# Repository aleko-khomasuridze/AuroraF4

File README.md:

# AuroraF4

AuroraF4 is a powerful development board based on the STM32F407VGT microcontroller, designed to provide developers with a feature-rich and compact solution for embedded system projects. This board is equipped with multiple peripherals, GPIOs, and expansion headers, making it ideal for both beginners and professionals.

## Features

- **Microcontroller**: STM32F407VGT
  - ARM Cortex-M4 processor
  - 168 MHz clock speed
  - 1 MB Flash, 192 KB SRAM
- **Interfaces**:
  - SPI, I2C, USART
  - JTAG/SWD debugging support
- **Peripherals**:
  - User-configurable LEDs (Green, Red, Yellow, Blue)
  - Reset (RST) and User (USR) buttons
  - Power input via USB-C or barrel jack
- **Expansion**:
  - Pin headers for GPIO access
  - 3.3V and GND pins available for peripherals
- **Power**:
  - Powered via USB-C or external 12V input

## Pinout Diagram

Refer to the pinout diagram above for GPIO assignments and interface connections.

## PCB Design and Layout

### PCB Top View

### 3D Render

## Getting Started

### Prerequisites

- Install [STM32CubeIDE](https://www.st.com/en/development-tools/stm32cubeide.html) for firmware development.
- Set up the STM32CubeMX tool for peripheral configuration.

### Powering the Board

1. Connect a USB-C cable to the power port.
2. Alternatively, use a 12V adapter through the barrel jack.

### Flashing Code

1. Connect the board to   your computer via USB.
2. Open STM32CubeIDE, configure your project for the STM32F407VGT.
3. Build and flash your program to the board.

### Debugging

Use the JTAG/SWD interface for debugging and programming. Ensure you have a compatible debugger like ST-Link V2.

## Applications

AuroraF4 is suitable for:
- Embedded systems prototyping
- IoT projects
- Robotics and automation
- Learning and experimentation with ARM Cortex-M4 architecture

## Resources

- [STM32F407VGT Datasheet](https://www.st.com/resource/en/datasheet/stm32f407vg.pdf)
- [STM32CubeIDE](https://www.st.com/en/development-tools/stm32cubeide.html)
- Pinout and Schematic: Refer to the `pinout.jpg` and PCB layout images in this repository.

## Credits

AuroraF4 is designed and assembled in Georgia by Aleko Khomasuridze.

---

For questions, suggestions, or contributions, feel free to open an issue or reach out.

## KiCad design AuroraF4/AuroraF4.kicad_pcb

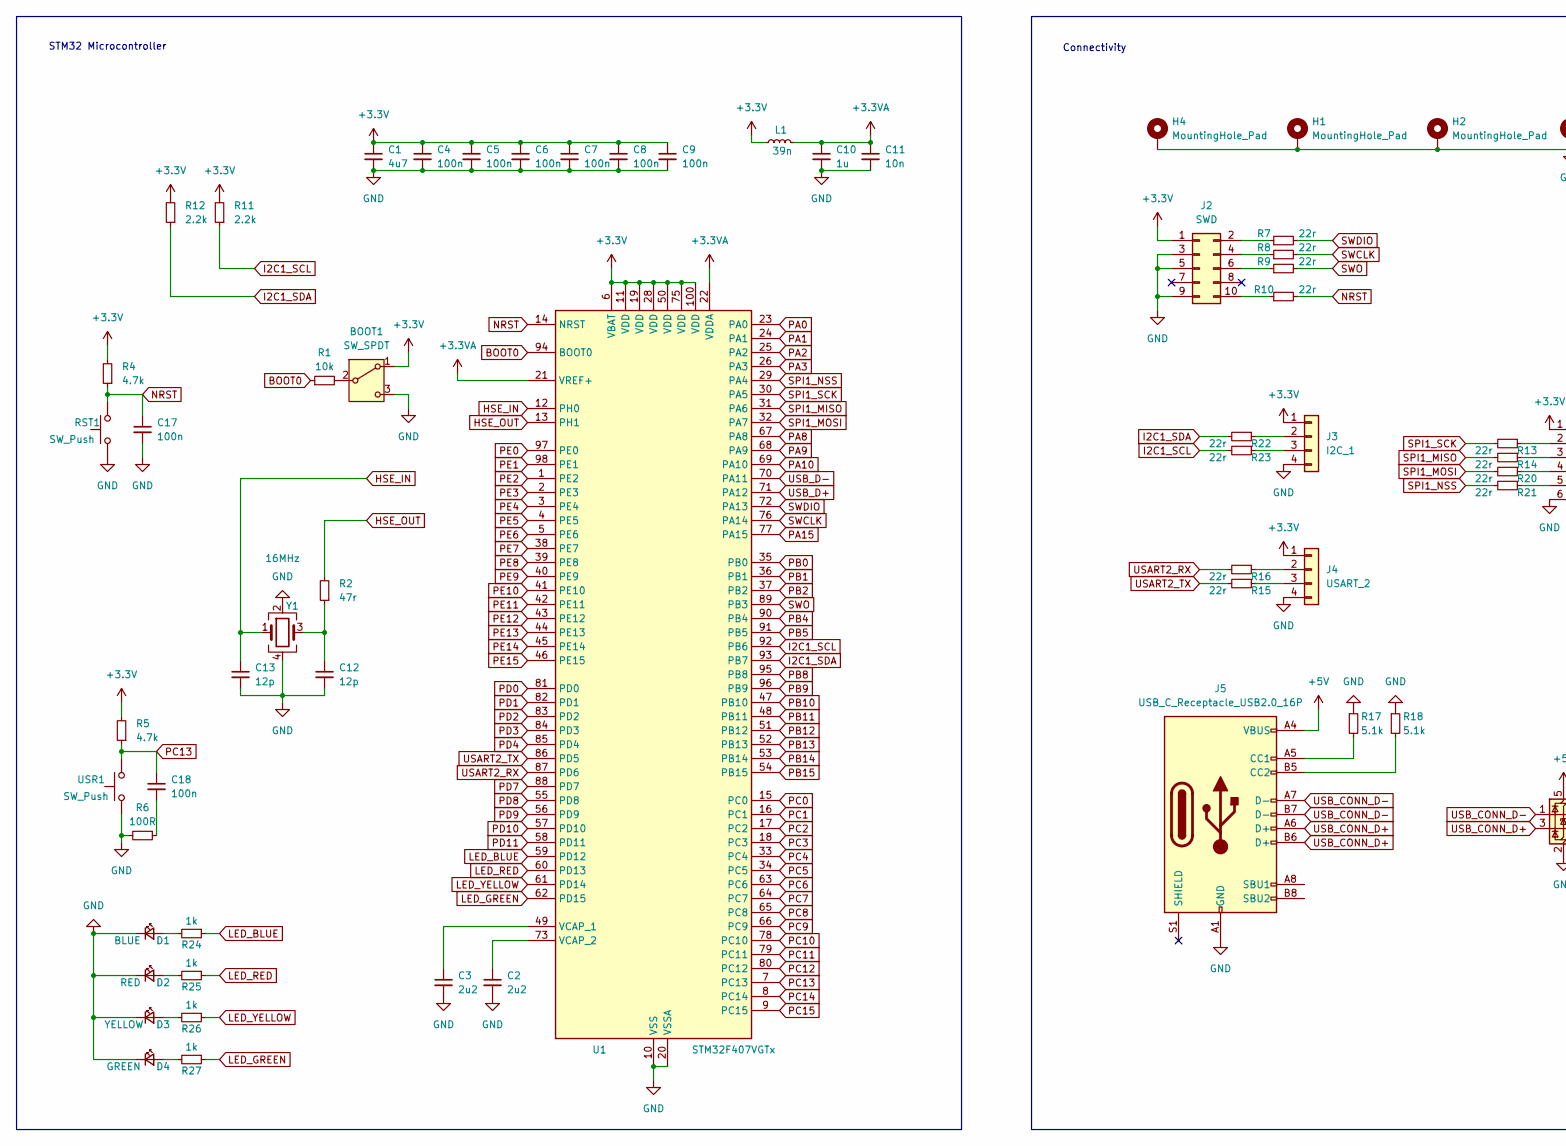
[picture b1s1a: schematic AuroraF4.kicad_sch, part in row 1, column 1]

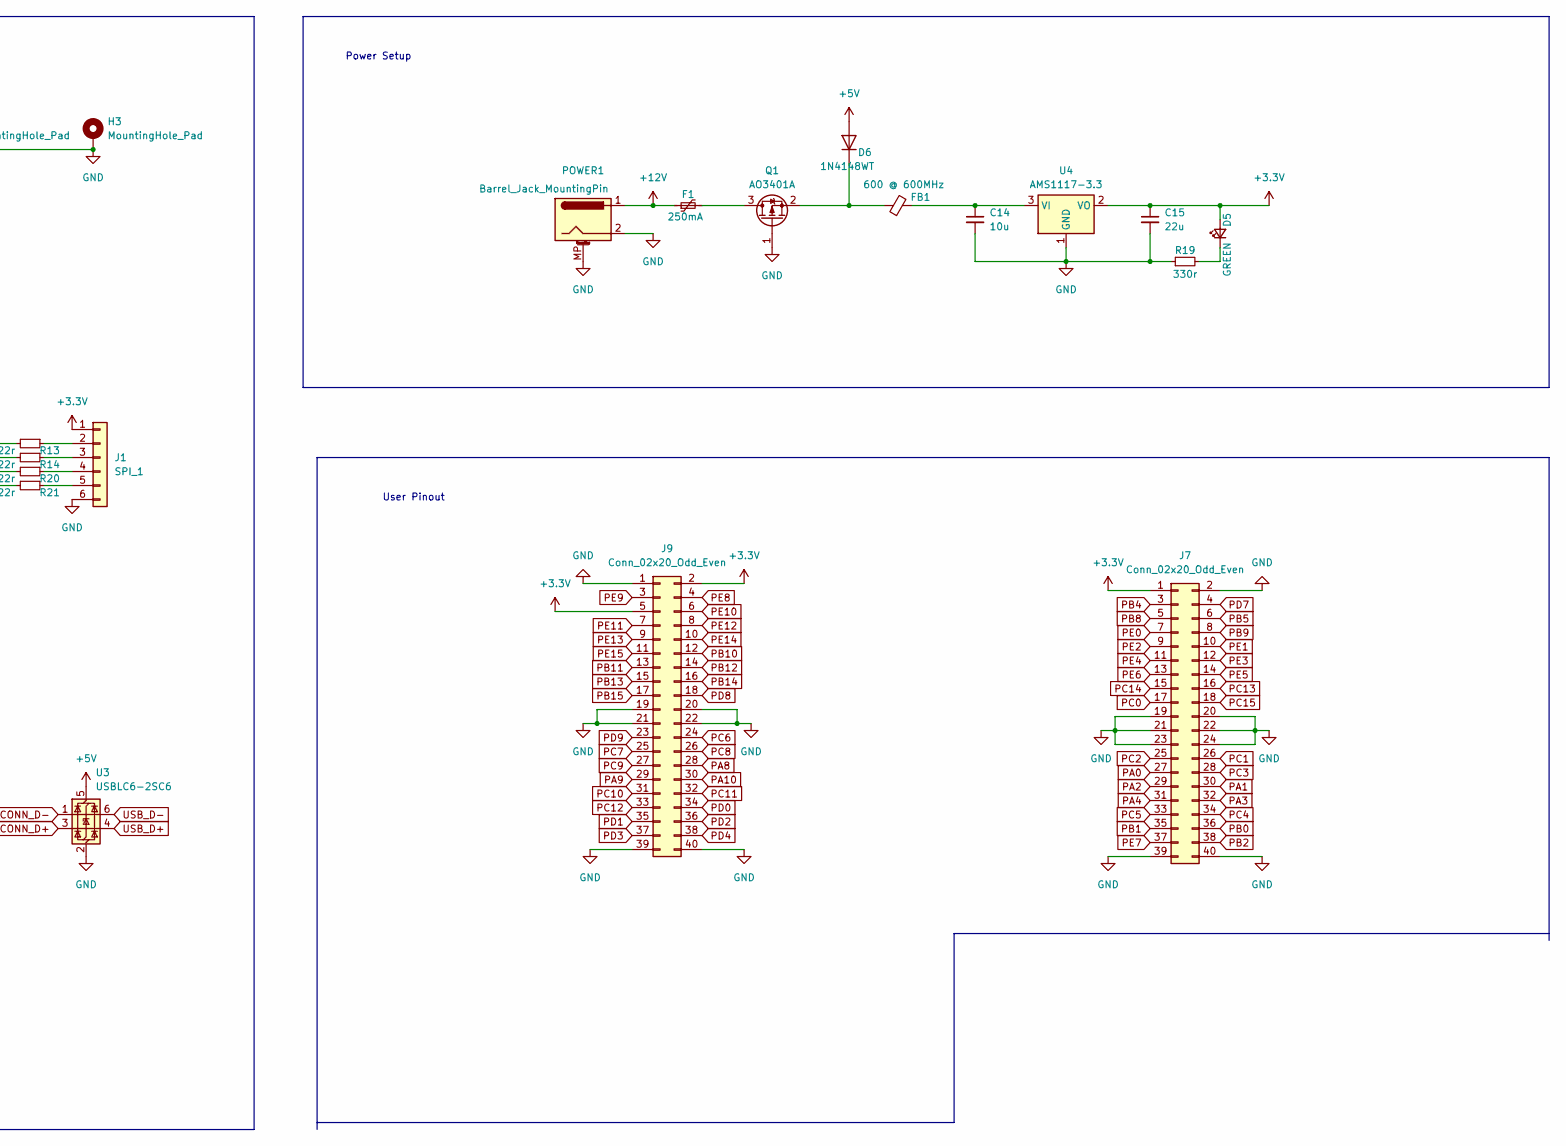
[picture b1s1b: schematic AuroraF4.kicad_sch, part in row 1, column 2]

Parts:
BOOT1: SW_SPDT; SW_SPDT_PCM12; LCSC Part # C221841
C1: 4u7; C_0603_1608Metric; LCSC Part # C1705
C2, C3: 2u2; C_0603_1608Metric; LCSC Part # C23630
C4, C5, C6, C7, C8, C9, C17, C18: 100n; C_0603_1608Metric; LCSC Part # C14663
C10: 1u; C_0603_1608Metric; LCSC Part # C1592
C11: 10n; C_0603_1608Metric; LCSC Part # C100042
C12, C13: 12p; C_0603_1608Metric; LCSC Part # C107034
C14: 10u; C_0805_2012Metric; LCSC Part # C5189822
C15: 22u; C_0805_2012Metric; LCSC Part # C29277
D1: BLUE; LED_0603_1608Metric; LCSC Part # C72041
D2: RED; LED_0603_1608Metric; LCSC Part # C72044
D3: YELLOW; LED_0603_1608Metric; LCSC Part # C72038
D4, D5: GREEN; LED_0603_1608Metric; LCSC Part # C72043
D6: 1N4148WT; D_SOD-123; LCSC Part # C963381
F1: 250mA; Fuse_1206_3216Metric; LCSC Part # C135328
FB1: 600 @ 600MHz; L_0805_2012Metric; LCSC Part # C1017
H1, H2, H3, H4: MountingHole_Pad; MountingHole_3.2mm_M3_Pad_Via
J1: SPI_1; JST-XA-1.25mm SMD Horizontal 01x06
J2: SWD; PinHeader_2x05_P1.27mm_Vertical_SMD; LCSC Part # C598540
J3: I2C_1; JST-XA-1.25mm SMD Horizontal 01x04
J4: USART_2; JST-XA-1.25mm SMD Horizontal 01x04
J5: USB_C_Receptacle_USB2.0_16P; USB_C_Receptacle_HCTL_HC-TYPE-C-16P-01A; LCSC Part # C39832533
J7, J9: Conn_02x20_Odd_Even; PinHeader_2x20_P2.54mm_Vertical
L1: 39n; L_0603_1608Metric; LCSC Part # C74308
POWER1: Barrel_Jack_MountingPin; BarrelJack_GCT_DCJ200-10-A_Horisontal; LCSC Part # C319099
Q1: AO3401A; SOT-23; LCSC Part # C347476
R1: 10k; R_0603_1608Metric; LCSC Part # C25804
R2: 47r; R_0603_1608Metric; LCSC Part # C23182
R4, R5: 4.7k; R_0603_1608Metric; LCSC Part # C105428
R6: 100R; R_0603_1608Metric; LCSC Part # C23345
R7, R8, R9, R10, R13, R14, R15, R16, R20, R21, R22, R23: 22r; R_0603_1608Metric; LCSC Part # C23345
R11, R12: 2.2k; R_0603_1608Metric; LCSC Part # C4190
R17, R18: 5.1k; R_0603_1608Metric; LCSC Part # C23186
R19: 330r; R_0603_1608Metric; LCSC Part # C23138
R24, R25, R26, R27: 1k; R_0603_1608Metric; LCSC Part # C25804
RST1: SW_Push; SW_SPST_B3U-1000P; LCSC Part # C843666
U1: STM32F407VGTx; LQFP-100_14x14mm_P0.5mm; LCSC Part # C12345
U3: USBLC6-2SC6; SOT-23-6; LCSC Part # C7519
U4: AMS1117-3.3; SOT-223-3_TabPin2; LCSC Part # C347222
USR1: SW_Push; SW_SPST_B3U-1000P; LCSC Part # C843666
Y1: 16MHz; Crystal_SMD_3225-4Pin_3.2x2.5mm; LCSC Part # C5917307

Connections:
+3.3V: BOOT1.1 (A), C1.1, C4.1, C5.1, C6.1, C7.1, C8.1, C9.1, C15.1, D5.2 (A), J1.1, J2.1, J3.1, J4.1, J7.1, J9.2, J9.5, L1.1, R4.2, R5.2, R11.2, R12.2, U1.6 (VBAT), U1.11 (VDD), U1.19 (VDD), U1.28 (VDD), U1.50 (VDD), U1.75 (VDD), U1.100 (VDD), U4.2 (VO)
+3.3VA: C10.1, C11.1, L1.2, U1.21 (VREF+), U1.22 (VDDA)
+5V: D6.2 (A), J5.A4 (VBUS), J5.A9 (VBUS), J5.B4 (VBUS), J5.B9 (VBUS), U3.5 (VBUS)
+12V: F1.1, POWER1.1; also elsewhere on the board
BOOT0: R1.1, U1.94 (BOOT0)
GND: BOOT1.3 (C), C1.2, C2.2, C3.2, C4.2, C5.2, C6.2, C7.2, C8.2, C9.2, C10.2, C11.2, C12.2, C13.2, C14.2, C15.2, C17.2, D1.1 (K), D2.1 (K), D3.1 (K), D4.1 (K), H1.1, H2.1, H3.1, H4.1, J1.6, J2.3, J2.5, J2.9, J3.4, J4.4, J5.A1 (GND), J5.A12 (GND), J5.B1 (GND), J5.B12 (GND), J7.2, J7.19, J7.20, J7.21, J7.22, J7.23, J7.24, J7.39, J7.40, J9.1, J9.19, J9.20, J9.21, J9.22, J9.39, J9.40, POWER1.2, POWER1.MP (MountPin), Q1.1 (G), R6.2, R17.1, R18.1, R19.1, RST1.1, U1.10 (VSS), U1.20 (VSSA), U1.27 (VSS), U1.74 (VSS), U1.99 (VSS), U3.2 (GND), U4.1 (GND), USR1.1, Y1.2, Y1.4; also elsewhere on the board
HSE_IN: C13.1, U1.12 (PH0), Y1.1
HSE_OUT: R2.2, U1.13 (PH1)
I2C1_SCL: R11.1, R23.2, U1.92 (PB6)
I2C1_SDA: R12.1, R22.2, U1.93 (PB7)
LED_BLUE: R24.1, U1.59 (PD12)
LED_GREEN: R27.1, U1.62 (PD15)
LED_RED: R25.1, U1.60 (PD13)
LED_YELLOW: R26.1, U1.61 (PD14)
NRST: C17.1, R4.1, R10.2, RST1.2, U1.14 (NRST); also elsewhere on the board
unnamed: BOOT1.2 (B), R1.2
unnamed: C12.1, R2.1, Y1.3
unnamed: C18.2, R6.1
unnamed: D1.2 (A), R24.2
unnamed: D2.2 (A), R25.2
unnamed: D3.2 (A), R26.2
unnamed: D4.2 (A), R27.2
unnamed: D5.1 (K), R19.2
unnamed: D6.1 (K), FB1.1, Q1.2 (S)
unnamed: J1.2, R13.1
unnamed: J1.3, R14.1
unnamed: J1.4, R20.1
unnamed: J1.5, R21.1
unnamed: J2.2, R7.1
unnamed: J2.4, R8.1
unnamed: J2.6, R9.1
unnamed: J2.10, R10.1
unnamed: J3.2, R22.1
unnamed: J3.3, R23.1
unnamed: J4.2, R16.1
unnamed: J4.3, R15.1
unnamed: J5.A5 (CC1), R17.2
unnamed: J5.B5 (CC2), R18.2
unnamed: F1.2, Q1.3 (D)
unnamed: C3.1, U1.49 (VCAP_1)
unnamed: C2.1, U1.73 (VCAP_2)
unnamed: C14.1, FB1.2, U4.3 (VI)
PA0: J7.27, U1.23 (PA0)
PA1: J7.30, U1.24 (PA1)
PA2: J7.29, U1.25 (PA2)
PA3: J7.32, U1.26 (PA3)
PA4: J7.31
PA8: J9.28, U1.67 (PA8)
PA9: J9.29, U1.68 (PA9)
PA10: J9.30, U1.69 (PA10)
PA15: U1.77 (PA15)
PB0: J7.36, U1.35 (PB0)
PB1: J7.35, U1.36 (PB1)
PB2: J7.38, U1.37 (PB2)
PB4: J7.3, U1.90 (PB4)
PB5: J7.6, U1.91 (PB5)
PB8: J7.5, U1.95 (PB8)
PB9: J7.8, U1.96 (PB9)
PB10: J9.12, U1.47 (PB10)
PB11: J9.13, U1.48 (PB11)
PB12: J9.14, U1.51 (PB12)
PB13: J9.15, U1.52 (PB13)
PB14: J9.16, U1.53 (PB14)
PB15: J9.17, U1.54 (PB15)
PC0: J7.17, U1.15 (PC0)
PC1: J7.26, U1.16 (PC1)
PC2: J7.25, U1.17 (PC2)
PC3: J7.28, U1.18 (PC3)
PC4: J7.34, U1.33 (PC4)
PC5: J7.33, U1.34 (PC5)
PC6: J9.24, U1.63 (PC6)
PC7: J9.25, U1.64 (PC7)
PC8: J9.26, U1.65 (PC8)
PC9: J9.27, U1.66 (PC9)
PC10: J9.31, U1.78 (PC10)
PC11: J9.32, U1.79 (PC11)
PC12: J9.33, U1.80 (PC12)
PC13: C18.1, J7.16, R5.1, U1.7 (PC13), USR1.2; also elsewhere on the board
PC14: J7.15, U1.8 (PC14)
PC15: J7.18, U1.9 (PC15)
PD0: J9.34, U1.81 (PD0)
PD1: J9.35, U1.82 (PD1)
PD2: J9.36, U1.83 (PD2)
PD3: J9.37, U1.84 (PD3)
PD4: J9.38, U1.85 (PD4)
PD7: J7.4, U1.88 (PD7)
PD8: J9.18, U1.55 (PD8)
PD9: J9.23, U1.56 (PD9)
PD10: U1.57 (PD10)
PD11: U1.58 (PD11)
PE0: J7.7, U1.97 (PE0)
PE1: J7.10, U1.98 (PE1)
PE2: J7.9, U1.1 (PE2)
PE3: J7.12, U1.2 (PE3)
PE4: J7.11, U1.3 (PE4)
PE5: J7.14, U1.4 (PE5)
PE6: J7.13, U1.5 (PE6)
PE7: J7.37, U1.38 (PE7)
PE8: J9.4, U1.39 (PE8)
PE9: J9.3, U1.40 (PE9)
PE10: J9.6, U1.41 (PE10)
PE11: J9.7, U1.42 (PE11)
PE12: J9.8, U1.43 (PE12)
PE13: J9.9, U1.44 (PE13)
PE14: J9.10, U1.45 (PE14)
PE15: J9.11, U1.46 (PE15)
SPI1_MISO: R14.2, U1.31 (PA6)
SPI1_MOSI: R20.2, U1.32 (PA7)
SPI1_NSS: R21.2, U1.29 (PA4)
SPI1_SCK: R13.2, U1.30 (PA5)
SWCLK: R8.2, U1.76 (PA14)
SWDIO: R7.2, U1.72 (PA13)
SWO: R9.2, U1.89 (PB3)
USART2_RX: R16.2, U1.87 (PD6)
USART2_TX: R15.2, U1.86 (PD5)
USB_CONN_D+: J5.A6 (D+), J5.B6 (D+), U3.3 (I/O2)
USB_CONN_D-: J5.A7 (D-), J5.B7 (D-), U3.1 (I/O1)
USB_D+: U1.71 (PA12), U3.4 (I/O2)
USB_D-: U1.70 (PA11), U3.6 (I/O1)

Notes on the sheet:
Power Setup
STM32 Microcontroller
Connectivity
User Pinout

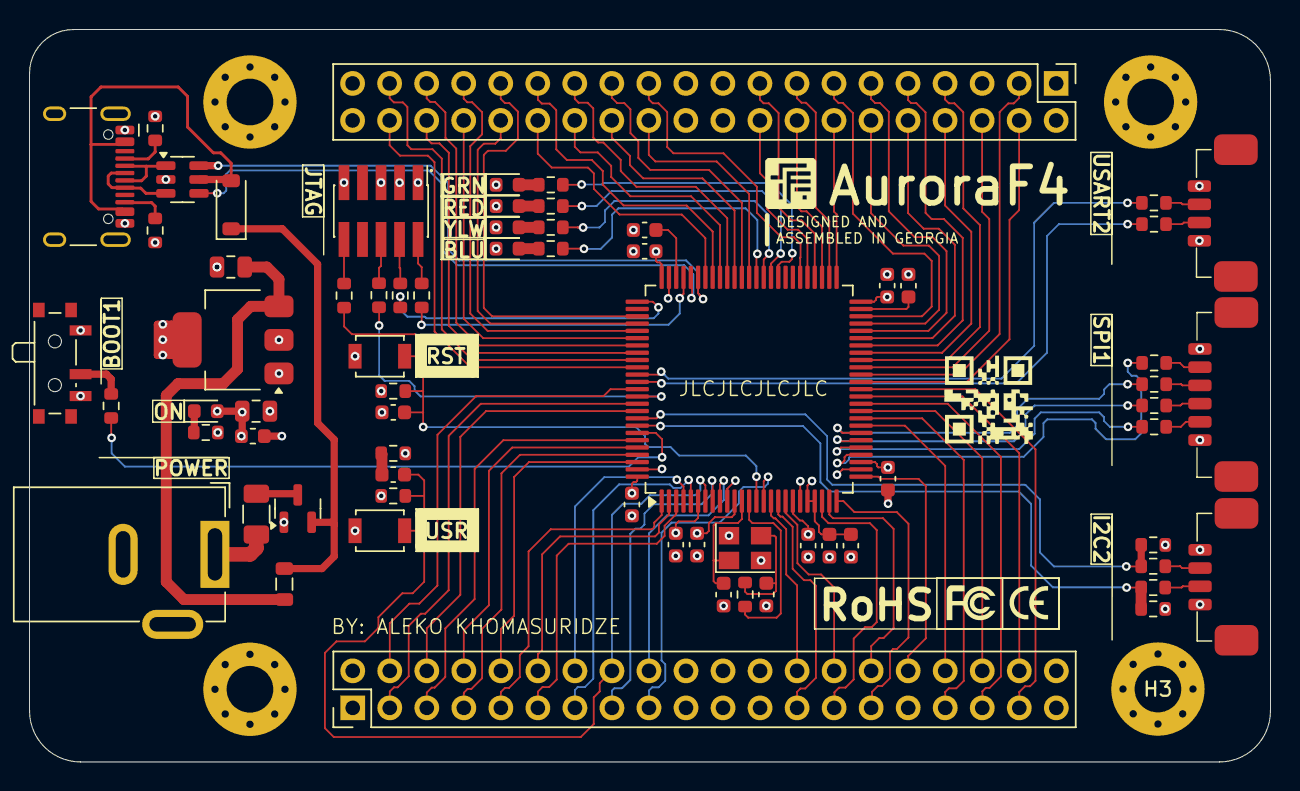
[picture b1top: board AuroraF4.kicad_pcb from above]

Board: 4 copper layers, 85.1 x 50.2 mm, 72 parts (0 on the bottom side), 115 nets.

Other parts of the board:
POWER: Barrel_Jack_MountingPin; BarrelJack_GCT_DCJ200-10-A_Horisontal
RST: SW_Push; SW_SPST_B3U-1000P
USR: SW_Push; SW_SPST_B3U-1000P

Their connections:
+12V: POWER.1; also elsewhere on the board
GND: POWER.2, RST.1, USR.1; also elsewhere on the board
NRST: RST.2; also elsewhere on the board
PC13: USR.2; also elsewhere on the board

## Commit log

2024-08-04 initilized PCB Prj
2024-08-07 initied Readme file
2024-08-07 Added reset boot I2C, SPI, UART, ETH to Sch
2024-08-07 added indicator lights to uart
2024-08-08 added Indicator LED and 2x20 male header to Sch
2024-08-08 PCB Update
2024-08-10 added stlink support to Sch and fixed layout of components on PCB
2024-08-10 createdd logo for board
2024-08-10 added some silk screen decorations to PCB
2024-08-11 started routing traces
2024-08-11 finished routing all the tracks
2024-08-12 started adding polygons to PCB and fixed some silk screen
2024-08-12 added silk screens on the top of the board
2024-08-13 finalized board v1.0.0
2024-08-13 fixed USB-C pads
2024-08-14 created a pinout documentation
2024-08-22 updated pcb and generated bom file
2024-12-29 complete AuroraF4 Board refactor
2025-01-01 fixed 3D models
2025-01-02 updated documentation
2025-03-06 backups
